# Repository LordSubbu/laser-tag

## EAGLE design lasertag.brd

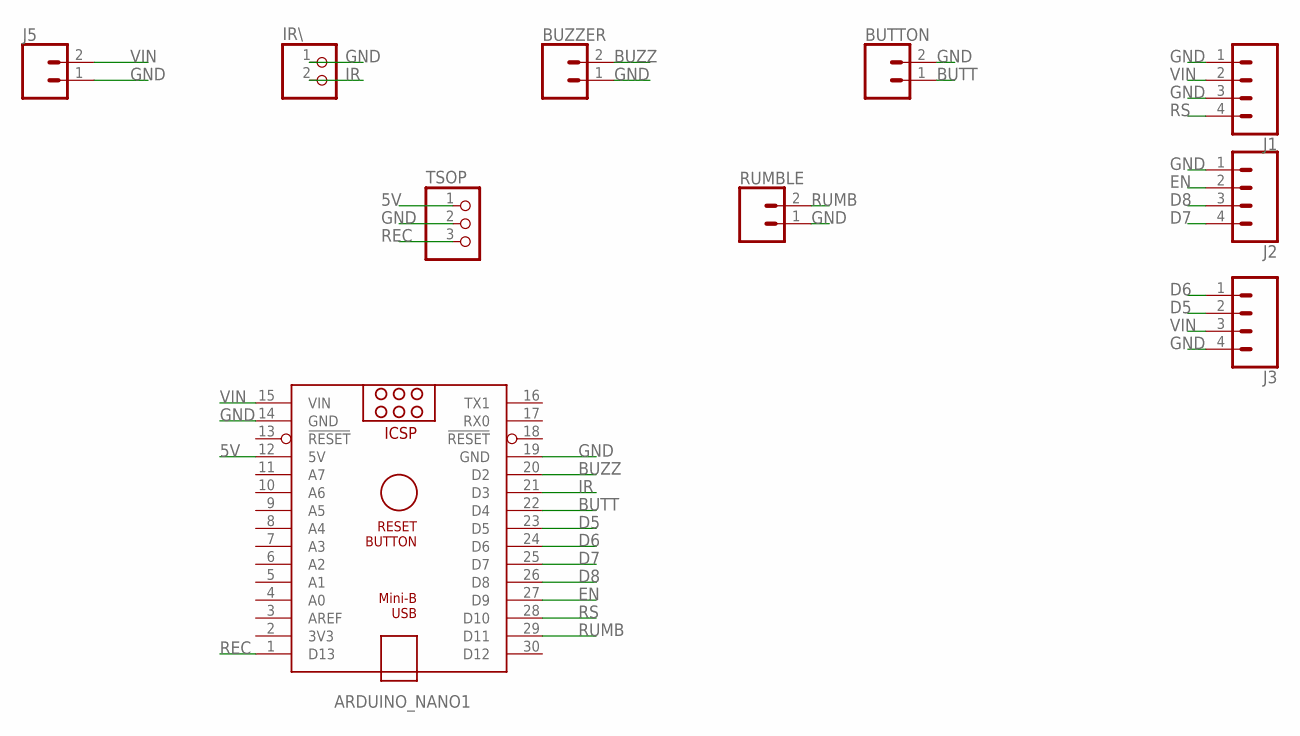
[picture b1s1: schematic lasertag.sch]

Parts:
ARDUINO_NANO1: ARDUINO_NANO
BUTTON: CONN_02; 1X02
BUZZER: CONN_02; 1X02
IR\: PINHD-1X2; 1X02
J1, J2, J3: CONN_04JST-PTH-VERT; JST-4-PTH-VERT
J5: CONN_02JST-PTH-VERT; JST-2-PTH-VERT
RUMBLE: CONN_02; 1X02
TSOP: PINHD-1X3; 1X03

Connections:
5V: ARDUINO_NANO1.12 (5V), TSOP.1
BUTT: ARDUINO_NANO1.22 (D4), BUTTON.1
BUZZ: ARDUINO_NANO1.20 (D2), BUZZER.2
D5: ARDUINO_NANO1.23 (D5), J3.2
D6: ARDUINO_NANO1.24 (D6), J3.1
D7: ARDUINO_NANO1.25 (D7), J2.4
D8: ARDUINO_NANO1.26 (D8), J2.3
EN: ARDUINO_NANO1.27 (D9), J2.2
GND: ARDUINO_NANO1.14 (GND), ARDUINO_NANO1.19 (GND), BUTTON.2, BUZZER.1, IR\.1, J1.1, J1.3, J2.1, J3.4, J5.1, RUMBLE.1, TSOP.2
IR: ARDUINO_NANO1.21 (D3), IR\.2
REC: ARDUINO_NANO1.1 (D13), TSOP.3
RS: ARDUINO_NANO1.28 (D10), J1.4
RUMB: ARDUINO_NANO1.29 (D11), RUMBLE.2
VIN: ARDUINO_NANO1.15 (VIN), J1.2, J3.3, J5.2

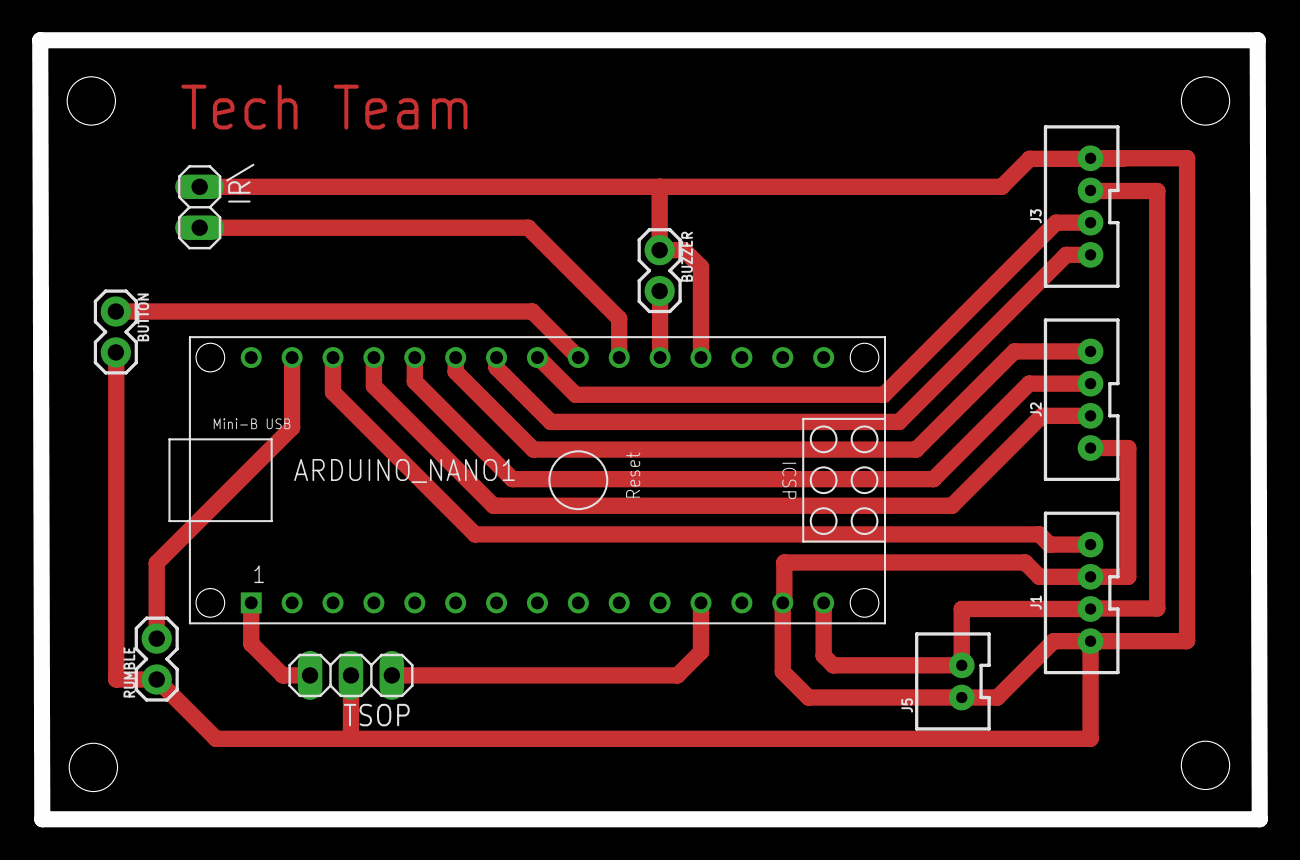
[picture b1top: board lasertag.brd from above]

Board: 2 copper layers, 75.8 x 48.4 mm, 10 parts (0 on the bottom side), 14 nets.

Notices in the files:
parts and their libraries:
SparkFun-Connectors: Licensing: Creative Commons ShareAlike 4.0 International - https://creativecommons.org/licenses/by-sa/4.0
